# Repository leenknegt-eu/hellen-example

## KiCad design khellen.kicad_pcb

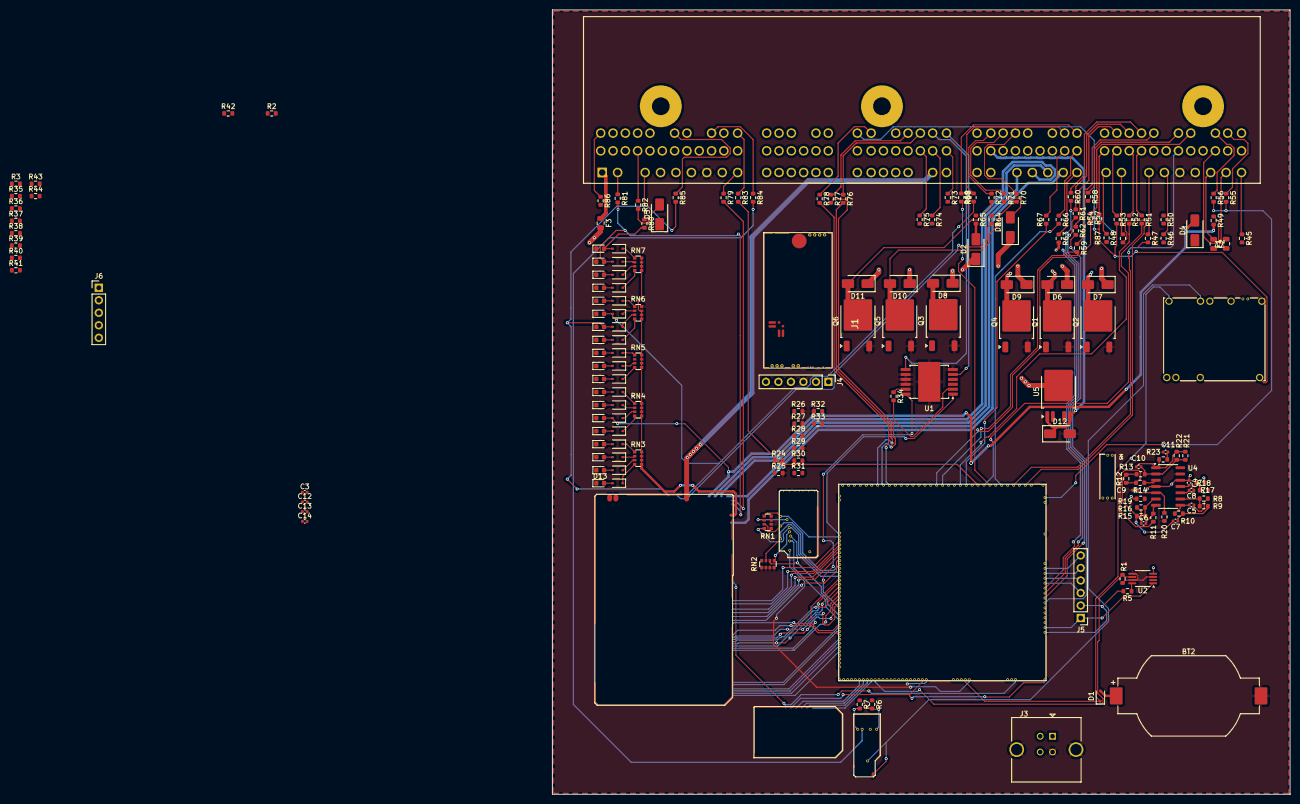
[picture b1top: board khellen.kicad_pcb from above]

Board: 4 copper layers, 149.8 x 159.2 mm, 182 parts (0 on the bottom side), 214 nets.

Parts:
BT2: CR2032; BatteryHolder_Renata_SMTU2032-LF_1x2032
C3, C14: 100n; C_0402_1005Metric
C4, C5, C6, C10, C11, C12: 10n; C_0402_1005Metric
C7, C8, C9: 33n; C_0402_1005Metric
C13: 10u; C_0402_1005Metric
D1, D14, D15, D17, D19, D21, D22, D23, D24, D29, D30, D32, D37, D38, D39, D40, D45, D46, D47, D48: 1N4148WS; D_SOD-323
D2, D3, D4, D5, D6, D7, D8, D9, D10, D11, D12: SS34; D_SMA
D13, D16, D18, D20, D25, D26, D27, D28, D33, D34, D36, D41, D42, D43, D44, D49, D50, D51, D52: LED_0603; LED_0603_1608Metric
F1, F2, F3: Fuse-Pad-Pad; Fuse_0805_2012Metric
J1: 1318612-1; TE_1318612-1
J3: USB_B; USB_B_TE_5787834_Vertical
J4: Conn_01x06; PinHeader_1x06_P2.54mm_Vertical
J5: Conn_01x06_Pin; PinHeader_1x06_P2.54mm_Vertical
J6: Conn_01x05_Pin; PinHeader_1x05_P2.54mm_Vertical
M1: Module-mega-mcu144-0.7; mega-mcu144
M2: Module-output-0.3; output
M3: Module-wbo-0.5; wbo
M4: Module-power_12and5V-0.3; power_12and5V
M5: Module-knock-0.2; knock
M6: Module-lin-0.1; lin
M7: Module-stlink-0.1; stlink
M8: Module-ign8-0.2; ign8
Q1, Q2, Q3, Q4, Q5, Q6: VND14NV04TR-E; TO-252-2
R1, R8, R16, R24, R25, R26, R27, R28, R29, R31, R34: 10k; R_0603_1608Metric
R2, R35, R37, R39, R40, R41: DNP; R_0603_1608Metric
R3, R36, R38, R42, R43, R44: 680k; R_0603_1608Metric
R5, R12, R30: 120; R_0603_1608Metric
R6, R7, R9, R10, R11, R13, R14, R15, R19, R20, R23, R33: 1k; R_0603_1608Metric
R17: 1.8k; R_0603_1608Metric
R18: 1.3k; R_0603_1608Metric
R21, R22: 47k; R_0603_1608Metric
R32: 4.7k; R_0603_1608Metric
R45, R46, R47, R48, R49, R50, R51, R52, R53, R54, R55, R56, R57, R58, R59, R60, R61, R62, R63, R64, R65, R66, R67, R68, R69, R70, R71, R72, R73, R74, R75, R76, R77, R78, R79, R80, R81, R82, R83, R84, R85, R86, R87: 0; R_0603_1608Metric
RN1, RN2: R_Pack04; R_Array_Convex_4x0612
RN3: 10k; R_Array_Convex_4x0612
RN4, RN5, RN6, RN7: 20k; R_Array_Convex_4x0612
U1: TLE9201SG; Infineon_PG-DSO-12-11
U2: DG470; MSOP-8_3x3mm_P0.65mm
U4: MCP6004; SOIC-14_3.9x8.7mm_P1.27mm
U5: BTS6143D; TO-252-4

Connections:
+3.3VA: M1.N28 (V33_SWITCHABLE), M8.V10 (V33)
+3V3: M1.N22 (V33), M1.N32 (V33), M7.N2 (V33), R31.2, R34.2, U1.2 (VSO)
+5V: M1.N31 (VCC), M2.W14 (V5), M4.E4 (V5), M7.N1 (V5)
+5VA: C4.1, M1.E38 (V5A_SWITCHABLE), M1.W2 (V5A_SWITCHABLE), M3.W1 (V5_IN), M5.E1 (V5A), M6.V3 (5V), M8.V9 (VCC), R2.1, R17.1, R19.1, R35.1, R37.1, R39.1, R40.1, R41.1, U4.4 (V+), U4.12 (+)
+5VP: J1.C22, M4.V4 (5VP), R53.2, R54.2
+12V: M4.E2 (V12), M6.N1 (12V), M6.V1 (12V)
+12V_PROT: M2.W5 (V12P), RN3.5 (R4.2), RN3.6 (R3.2), RN3.7 (R2.2), RN3.8 (R1.2), RN4.5 (R4.2), RN4.6 (R3.2), RN4.7 (R2.2), RN4.8 (R1.2), RN5.5 (R4.2), RN5.6 (R3.2), RN5.7 (R2.2), RN5.8 (R1.2), RN6.5 (R4.2), RN6.6 (R3.2), RN6.7 (R2.2), RN7.5 (R4.2), RN7.6 (R3.2), RN7.7 (R2.2), RN7.8 (R1.2)
+12V_RAW: C3.2, C13.1, C14.1, D2.1 (K), D3.1 (K), D4.1 (K), D5.1 (K), D6.1 (K), D7.1 (K), D8.1 (K), D9.1 (K), D10.1 (K), D11.1 (K), F1.2, F2.2, J1.C2, M2.S11 (V12_RAW), M4.V3 (V12_RAW), R63.2, U1.4 (VS), U2.4 (V+), U5.3 (Vbb)
/4WIRE_DENSO_SIGNAL+: C7.2, R12.2, R13.1, R15.2, R46.2
/4WIRE_DENSO_SIGNAL-: C7.1, R9.2, R10.2, R50.2
/AC_LS: M1.E31 (OUT_INJ5), M2.W18 (INJ5)
/AIN1: M1.S13 (IN_AUX1), R2.2, R3.1, R75.2
/AIN2: M1.S12 (IN_AUX2), R35.2, R36.1, R74.2
/AIN3: M1.S11 (IN_AUX3), R37.2, R38.1, R73.2
/ALTERNATOR_CONTROL_LS: D39.2 (A), D43.2 (K), M2.S10 (OUT_LOW11), R69.2
/AUX_LS1: M8.S4 (OUT_IGN5), Q4.1 (G), R27.1
/AUX_LS2: M8.S6 (OUT_IGN3), Q2.1 (G), R25.1
/AUX_LS3: M8.S5 (OUT_IGN4), Q1.1 (G), R24.1
/CAN_H: J1.C15, J5.1, M1.W12 (CANH), M3.W4 (CANH), U2.1
/CAN_L: J1.C14, J5.2, M1.W13 (CANL), M3.W3 (CANL), R5.2
/DC_DIR: M1.E36 (IO7), U1.1 (DIR)
/DC_DIS: M1.N23 (IO5), R34.1, U1.11 (DIS)
/DC_PWM: M1.E17 (OUT_PWM2), U1.12 (PWM)
/DENSO/OUT: C11.1, M1.S15 (IN_O2S2), R23.2
/DIN1: M1.S9 (IN_SENS1), R39.2, R42.1, R78.2
/DIN2: M1.S8 (IN_SENS2), R40.2, R43.1, R77.2
/DIN3: M1.S7 (IN_SENS3), R41.2, R44.1, R76.2
/IDLE_AIR: M1.E32 (OUT_INJ6), M2.W17 (INJ6)
/INTAKE_RUNNER: M1.E33 (OUT_INJ7), M2.W16 (INJ7)
/IN_BRAKE: M1.S24 (IN_CAM), R83.2
/IN_CAM_SYNC_HALL: D30.2 (A), D34.2 (K), M1.S14 (IN_RES2), R58.2
/IN_CLT: M1.S28 (IN_CLT), R66.2
/IN_CRANK_HALL: D29.2 (A), D33.2 (K), M1.S17 (IN_RES1), R47.2
/IN_IAT: M1.S26 (IN_IAT), R68.2
/IN_INTAKE_POSITION: M1.S32 (IN_TPS2), R48.2
/IN_KNOCK: M5.W1 (IN_KNOCK), R87.2
/IN_MAP: M1.S21 (IN_MAP1), R52.2
/IN_TPS: J1.A15, M1.S30 (IN_TPS)
/IN_VIGN: F3.2, M4.V2 (IN_VIGN)
/IN_VSS: M1.S25 (IN_VSS), R51.2
/IN_VTEC_PRESSURE_SW: M1.S22 (IN_CRANK), R67.2
/IN_VVT_CAM_HALL: D32.2 (A), D36.2 (K), M1.S18 (IN_RES3), R57.2
/LIN: M6.V4 (LIN), R84.2
/LOCKOUT_SOLENOID: M1.E34 (OUT_INJ8), M2.W15 (INJ8)
/LS_EVAP: M8.S2 (OUT_IGN7), Q5.1 (G), R28.1
/MCU_AUX_01: M1.E35 (IO6), M8.V8 (IGN1), RN1.5 (R4.2)
/MCU_AUX_02: M1.N24 (UART8_RX), M8.V7 (IGN2), RN1.6 (R3.2)
/MCU_AUX_LS1: M8.V4 (IGN5), RN2.5 (R4.2)
/MCU_AUX_LS2: M1.E25 (OUT_PWM7), M8.V5 (IGN4), RN1.8 (R1.2)
/MCU_AUX_LS3: M1.E28 (OUT_PWM8), M8.V6 (IGN3), RN1.7 (R2.2)
/MCU_LS_EVAP: M1.E26 (OUT_PWM6), M8.V2 (IGN7), RN2.7 (R2.2)
/MCU_VTC_LS: M1.E14 (OUT_PWM5), M8.V1 (IGN8), RN2.8 (R1.2)
/MCU_WBO_HEATER_LOW_SIDE: M1.E15 (OUT_PWM4), M8.V3 (IGN6), RN2.6 (R3.2)
/OUT_AC_LS: D5.2 (A), D21.2 (A), D25.2 (K), M2.W10 (OUT_INJ5), R82.2
/OUT_AUX_LS1: D9.2 (A), J1.C13, Q4.2 (D)
/OUT_AUX_LS2: D7.2 (A), J1.C12, Q2.2 (D)
/OUT_AUX_LS3: D6.2 (A), J1.C11, Q1.2 (D)
/OUT_CHECK_ENGINE: D37.2 (A), D41.2 (K), M2.S14 (OUT_LOW9), R86.2
/OUT_DCn: J1.C16, U1.5 (OUT1)
/OUT_DCp: J1.C17, U1.7 (OUT2)
/OUT_FUEL_RELAY: D46.2 (A), D50.2 (K), M2.W1 (OUT_LOW2), R79.2
/OUT_IDLE_AIR: D4.2 (A), D22.2 (A), D26.2 (K), M2.S15 (OUT_INJ6), R49.2
/OUT_IGN1: M1.W11 (IGN1), R62.2
/OUT_IGN2: M1.W10 (IGN2), R61.2
/OUT_IGN3: M1.W9 (IGN3), R60.2
/OUT_IGN4: M1.W8 (IGN4), R59.2
/OUT_INJ1: D19.2 (A), D20.2 (K), J1.B5, M2.S18 (OUT_INJ1)
/OUT_INJ2: D17.2 (A), D18.2 (K), J1.B4, M2.S16 (OUT_INJ2)
/OUT_INJ3: D15.2 (A), D16.2 (K), J1.B3, M2.S17 (OUT_INJ3)
/OUT_INJ4: D13.2 (K), D14.2 (A), J1.B2, M2.W7 (OUT_INJ4)
/OUT_INTAKE_RUNNER: D3.2 (A), D23.2 (A), D27.2 (K), M2.W12 (OUT_INJ7), R71.2
/OUT_LOCKOUT_SOLENOID: D2.2 (A), D24.2 (A), D28.2 (K), M2.W11 (OUT_INJ8), R65.2
/OUT_LS_EVAP: D10.2 (A), Q5.2 (D), R70.2
/OUT_MAIN_RELAY_CONTROL: D48.2 (A), D52.2 (K), M2.W13 (OUT_LOW5_MAIN), R80.2
/OUT_RADIATOR_RELAY: D45.2 (A), D49.2 (K), M2.S8 (OUT_LOW1), R64.2
/OUT_TACHOMETER: D38.2 (A), D42.2 (K), M2.S6 (OUT_PP2), R85.2
/OUT_VTC_LS: D11.2 (A), Q6.2 (D), R72.2
/OUT_VTS_HS: C12.1, D12.1 (K), D40.2 (A), D44.2 (K), J1.B15, R32.2, U5.1 (OUT), U5.5 (OUT)
/OUT_WBO_HEATER_LOW_SIDE: D8.2 (A), Q3.2 (D), R45.2
/V33_REF: M1.W3 (V33_REF), M3.W9 (VDDA)
/VREF2: M1.S5 (VREF2), M5.W2 (VREF)
/VTC_LS: M8.S1 (OUT_IGN8), Q6.1 (G), R29.1
/VTS_HS: M2.S12 (OUT_LOW8_PULLUP), U5.2 (IN)
/WBO_HEATER_LOW_SIDE: M8.S3 (OUT_IGN6), Q3.1 (G), R26.1
/WBO_RELAY_OUTPUT_LS: D47.2 (A), D51.2 (K), M2.W2 (OUT_LOW10), R81.2
GND: BT2.2 (-), C3.1, C4.2, C8.1, C9.1, C11.2, C12.2, C13.2, C14.2, D12.2 (A), J1.A4, J1.A5, J1.C20, J1.E3, J3.4 (GND), J3.5 (Shield), J4.3, J6.4, J6.5, M1.G (GND), M2.G (GND), M2.S3 (GND), M3.E6 (LSU_H-), M3.G (GND), M4.S1 (GND), M5.E2 (GND), M6.E1 (GND), M6.S1 (GND), M7.G (GND), M8.G (GND), Q1.3 (S), Q2.3 (S), Q3.3 (S), Q4.3 (S), Q5.3 (S), Q6.3 (S), R1.2, R18.2, R20.2, R24.2, R25.2, R26.2, R27.2, R28.2, R29.2, R30.1, R32.1, R33.2, RN1.1 (R1.1), RN1.2 (R2.1), RN1.3 (R3.1), RN1.4 (R4.1), RN2.1 (R1.1), RN2.2 (R2.1), RN2.3 (R3.1), RN2.4 (R4.1), RN6.8 (R1.2), U1.6 (GND), U1.8 (SI), U1.9 (CSN), U1.10 (SCK), U1.13 (GND), U2.3 (GND), U2.5 (~EN), U2.7 (V-), U4.11 (V-), U4.13 (-)
GNDA: J1.A10, J1.A11, M1.E39 (GNDA), M1.W1 (GNDA), R3.2, R36.2, R38.2, R42.2, R43.2, R44.2, R55.2, R56.2
unnamed: BT2.1 (+), D1.2 (A)
unnamed: C5.1, R8.2
unnamed: C5.2, R10.1, U4.8
unnamed: C6.1, R16.2
unnamed: C6.2, R11.1, U4.7
unnamed: C10.2, R21.2, R22.2, R23.1, U4.1
unnamed: D1.1 (K), M1.N27 (VBAT), M4.E1 (VBAT)
unnamed: D13.1 (A), D14.1 (K), RN3.4 (R4.1)
unnamed: D15.1 (K), D16.1 (A), RN3.3 (R3.1)
unnamed: D17.1 (K), D18.1 (A), RN3.2 (R2.1)
unnamed: D19.1 (K), D20.1 (A), RN3.1 (R1.1)
unnamed: D21.1 (K), D25.1 (A), RN4.4 (R4.1)
unnamed: D22.1 (K), D26.1 (A), RN4.3 (R3.1)
unnamed: D23.1 (K), D27.1 (A), RN4.2 (R2.1)
unnamed: D24.1 (K), D28.1 (A), RN4.1 (R1.1)
unnamed: D29.1 (K), D33.1 (A), RN5.4 (R4.1)
unnamed: D30.1 (K), D34.1 (A), RN5.3 (R3.1)
unnamed: D32.1 (K), D36.1 (A), RN5.1 (R1.1)
unnamed: D37.1 (K), D41.1 (A), RN6.4 (R4.1)
unnamed: D38.1 (K), D42.1 (A), RN6.3 (R3.1)
unnamed: D39.1 (K), D43.1 (A), RN6.2 (R2.1)
unnamed: D40.1 (K), D44.1 (A), RN6.1 (R1.1)
unnamed: D45.1 (K), D49.1 (A), RN7.4 (R4.1)
unnamed: D46.1 (K), D50.1 (A), RN7.3 (R3.1)
unnamed: D47.1 (K), D51.1 (A), RN7.2 (R2.1)
unnamed: D48.1 (K), D52.1 (A), RN7.1 (R1.1)
unnamed: F1.1, J1.A2
unnamed: F2.1, J1.A3
unnamed: F3.1, J1.E9
unnamed: J1.A1, R45.1
unnamed: J1.A6, R46.1
unnamed: J1.A7, R47.1
unnamed: J1.A8, R48.1
unnamed: J1.A9, R87.1
unnamed: J1.A12, R49.1
unnamed: J1.A16, R50.1
unnamed: J1.A18, R51.1
unnamed: J1.A19, R52.1
unnamed: J1.A20, R53.1
unnamed: J1.A21, R54.1
unnamed: J1.A23, R55.1
unnamed: J1.A24, R56.1
unnamed: J1.A25, R57.1
unnamed: J1.A26, R58.1
unnamed: J1.A27, R59.1
unnamed: J1.A28, R60.1
unnamed: J1.A29, R61.1
unnamed: J1.A30, R62.1
unnamed: J1.B1, R63.1
unnamed: J1.B6, R64.1
unnamed: J1.B7, R65.1
unnamed: J1.B8, R66.1
unnamed: J1.B9, R67.1
unnamed: J1.B17, R68.1
unnamed: J1.B18, R69.1
unnamed: J1.B21, R70.1
unnamed: J1.B22, R71.1
unnamed: J1.B23, R72.1
unnamed: J1.C8, R73.1
unnamed: J1.C9, R74.1
unnamed: J1.C10, R75.1
unnamed: J1.C18, R76.1
unnamed: J1.C19, R77.1
unnamed: J1.C21, R78.1
unnamed: J1.E1, R79.1
unnamed: J1.E7, R80.1
unnamed: J1.E8, R81.1
unnamed: J1.E18, R82.1
unnamed: J1.E22, R83.1
unnamed: J1.E24, R84.1
unnamed: J1.E26, R85.1
unnamed: J1.E31, R86.1
unnamed: J3.3 (D+), J6.3, M1.N3 (USBP)
unnamed: J3.2 (D-), J6.2, M1.N2 (USBM)
unnamed: J3.1 (VBUS), J6.1, M1.N4 (VBUS)
unnamed: J4.1, M3.W8 (V33_OUT)
unnamed: J4.2, M3.W7 (SWCLK)
unnamed: J4.4, M3.W6 (SWDIO)
unnamed: J4.5, M3.W5 (nReset)
unnamed: J5.3, M1.W7 (IGN5)
unnamed: J5.4, M1.W6 (IGN6)
unnamed: J5.5, M1.W5 (IGN7)
unnamed: J5.6, M1.W4 (IGN8)
unnamed: M1.S1 (IN_D4), M4.E6 (PG_5VP)
unnamed: M1.S23 (IN_KNOCK), M5.E3 (OUT_KNOCK)
unnamed: M1.N26 (IN_VIGN), M4.E3 (VIGN)
unnamed: M1.E19 (OUT_INJ1), M2.W24 (INJ1)
unnamed: M1.E18 (OUT_INJ2), M2.W23 (INJ2)
unnamed: M1.E29 (OUT_INJ3), M2.W20 (INJ3)
unnamed: M1.E30 (OUT_INJ4), M2.W19 (INJ4)
unnamed: M1.E8 (OUT_IO1), M2.W38 (LOW3_DUAL)
unnamed: M1.E12 (OUT_IO2), M2.W34 (LOW4_DUAL)
unnamed: M1.E6 (OUT_IO3), M2.W40 (LOW5_MAIN)
unnamed: M1.E21 (OUT_IO4), M2.W25 (LOW6_DIODE)
unnamed: M1.E7 (OUT_IO5), M2.W39 (LOW7_HIGH1)
unnamed: M1.E9 (OUT_IO6), M2.W37 (LOW8_HIGH2)
unnamed: M1.E23 (OUT_IO7), M2.W27 (LOW9)
unnamed: M1.E22 (OUT_IO8), M2.W26 (LOW10)
unnamed: M1.E11 (OUT_IO9), M2.W35 (LOW11)
unnamed: M1.E10 (OUT_IO10), M2.W22 (PP2)
unnamed: M1.E24 (OUT_IO11), M2.W28 (PP1)
unnamed: M1.E13 (OUT_IO12), M2.W21 (LOW1)
unnamed: M1.E20 (OUT_IO13), M2.W29 (LOW2)
unnamed: M1.N29 (OUT_PWR_EN), M4.E5 (EN_5VP)
unnamed: M1.N10 (SPI3_CS), R1.1, U2.6
unnamed: M1.N8 (SWCLK), M7.N5 (SWCLK)
unnamed: M1.N7 (SWDIO), M7.N4 (SWDIO)
unnamed: M1.N6 (SWO), M7.N3 (SWO)
unnamed: M1.N18 (UART2_RX), R6.1
unnamed: M1.N17 (UART2_TX), R7.1
unnamed: M1.N9 (nReset), M7.N6 (nReset)
unnamed: J1.C7, M3.E5 (LSU_H+)
unnamed: J1.C5, M3.E3 (LSU_Ip)
unnamed: J1.C4, M3.E4 (LSU_Rtrim)
unnamed: J1.C3, M3.E1 (LSU_Un)
unnamed: J1.C6, M3.E2 (LSU_Vm)
unnamed: M6.V2 (UART_RX), R6.2
unnamed: M6.V5 (UART_TX), R7.2
unnamed: R5.1, U2.8
unnamed: R11.2, R12.1, R14.1
unnamed: R14.2, U4.3 (+)
unnamed: C10.1, R13.2, R21.1, R22.1, U4.2 (-)
unnamed: C9.2, R19.2, R20.1, U4.5 (+)
unnamed: R15.1, R16.1, U4.6 (-)
unnamed: C8.2, R17.2, R18.1, U4.10 (+)
unnamed: R8.1, R9.1, U4.9 (-)
unnamed: R33.1, U5.4 (IS)

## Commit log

2025-05-07 Schematic updated
2025-05-08 Updated PCB, updated schematic
2025-05-08 updated PCB
2025-05-08 Update kicad6-libraries
2025-05-09 changed file structure
